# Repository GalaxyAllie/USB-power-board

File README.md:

# USB-power-board
A tiny little board to expose 5V

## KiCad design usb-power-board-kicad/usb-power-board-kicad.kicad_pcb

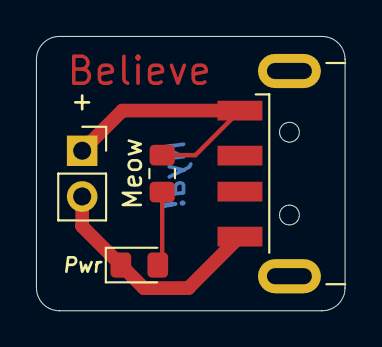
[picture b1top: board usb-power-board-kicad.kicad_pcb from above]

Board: 2 copper layers, 17.1 x 15.2 mm, 4 parts (0 on the bottom side), 3 nets.

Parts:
+: Fan; PinSocket_1x02_P2.54mm_Vertical
J1: USB_A; USB_A_CNCTech_1001-011-01101_Horizontal
Meow: R; R_0805_2012Metric_Pad1.15x1.40mm_HandSolder
Pwr: LED; LED_0805_2012Metric_Pad1.15x1.40mm_HandSolder

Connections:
+5V: +.1, J1.1, Meow.2
GND: +.2, J1.4, Pwr.1
unnamed: Meow.1, Pwr.2

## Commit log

2020-07-25 board
